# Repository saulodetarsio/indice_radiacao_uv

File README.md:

# Protótipo de um medidor de índice de radiação UV

Primeira parte do projeto

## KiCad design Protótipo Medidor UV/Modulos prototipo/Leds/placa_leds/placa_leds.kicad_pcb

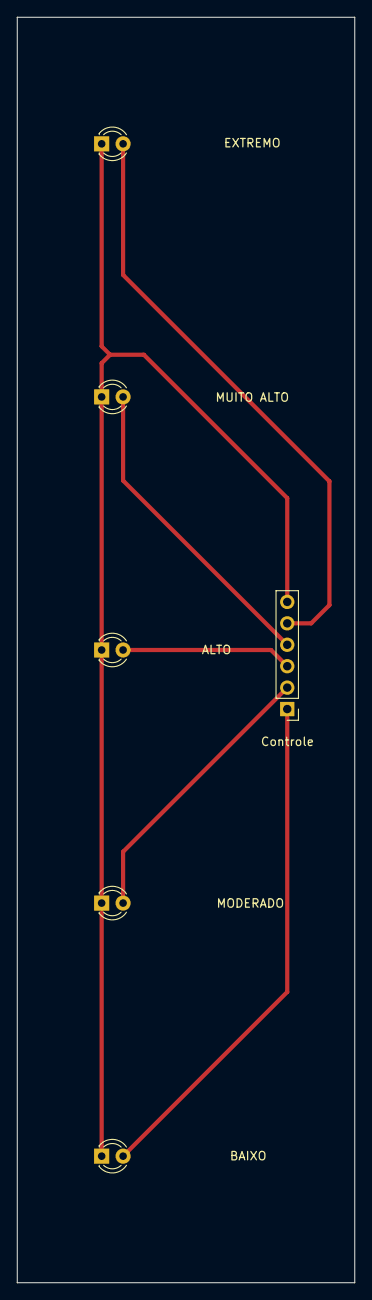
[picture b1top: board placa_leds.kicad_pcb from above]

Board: 2 copper layers, 40.0 x 150.0 mm, 6 parts (0 on the bottom side), 6 nets.

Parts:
ALTO: LED; LED_D3.0mm
BAIXO: LED; LED_D3.0mm
Controle: Conn_01x06_Male; PinHeader_1x06_P2.54mm_Vertical
EXTREMO: LED; LED_D3.0mm
MODERADO: LED; LED_D3.0mm
MUITO ALTO: LED; LED_D3.0mm

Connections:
unnamed: ALTO.1, BAIXO.1, Controle.6, EXTREMO.1, MODERADO.1, MUITO ALTO.1
unnamed: BAIXO.2, Controle.1
unnamed: Controle.2, MODERADO.2
unnamed: ALTO.2, Controle.3
unnamed: Controle.4, MUITO ALTO.2
unnamed: Controle.5, EXTREMO.2

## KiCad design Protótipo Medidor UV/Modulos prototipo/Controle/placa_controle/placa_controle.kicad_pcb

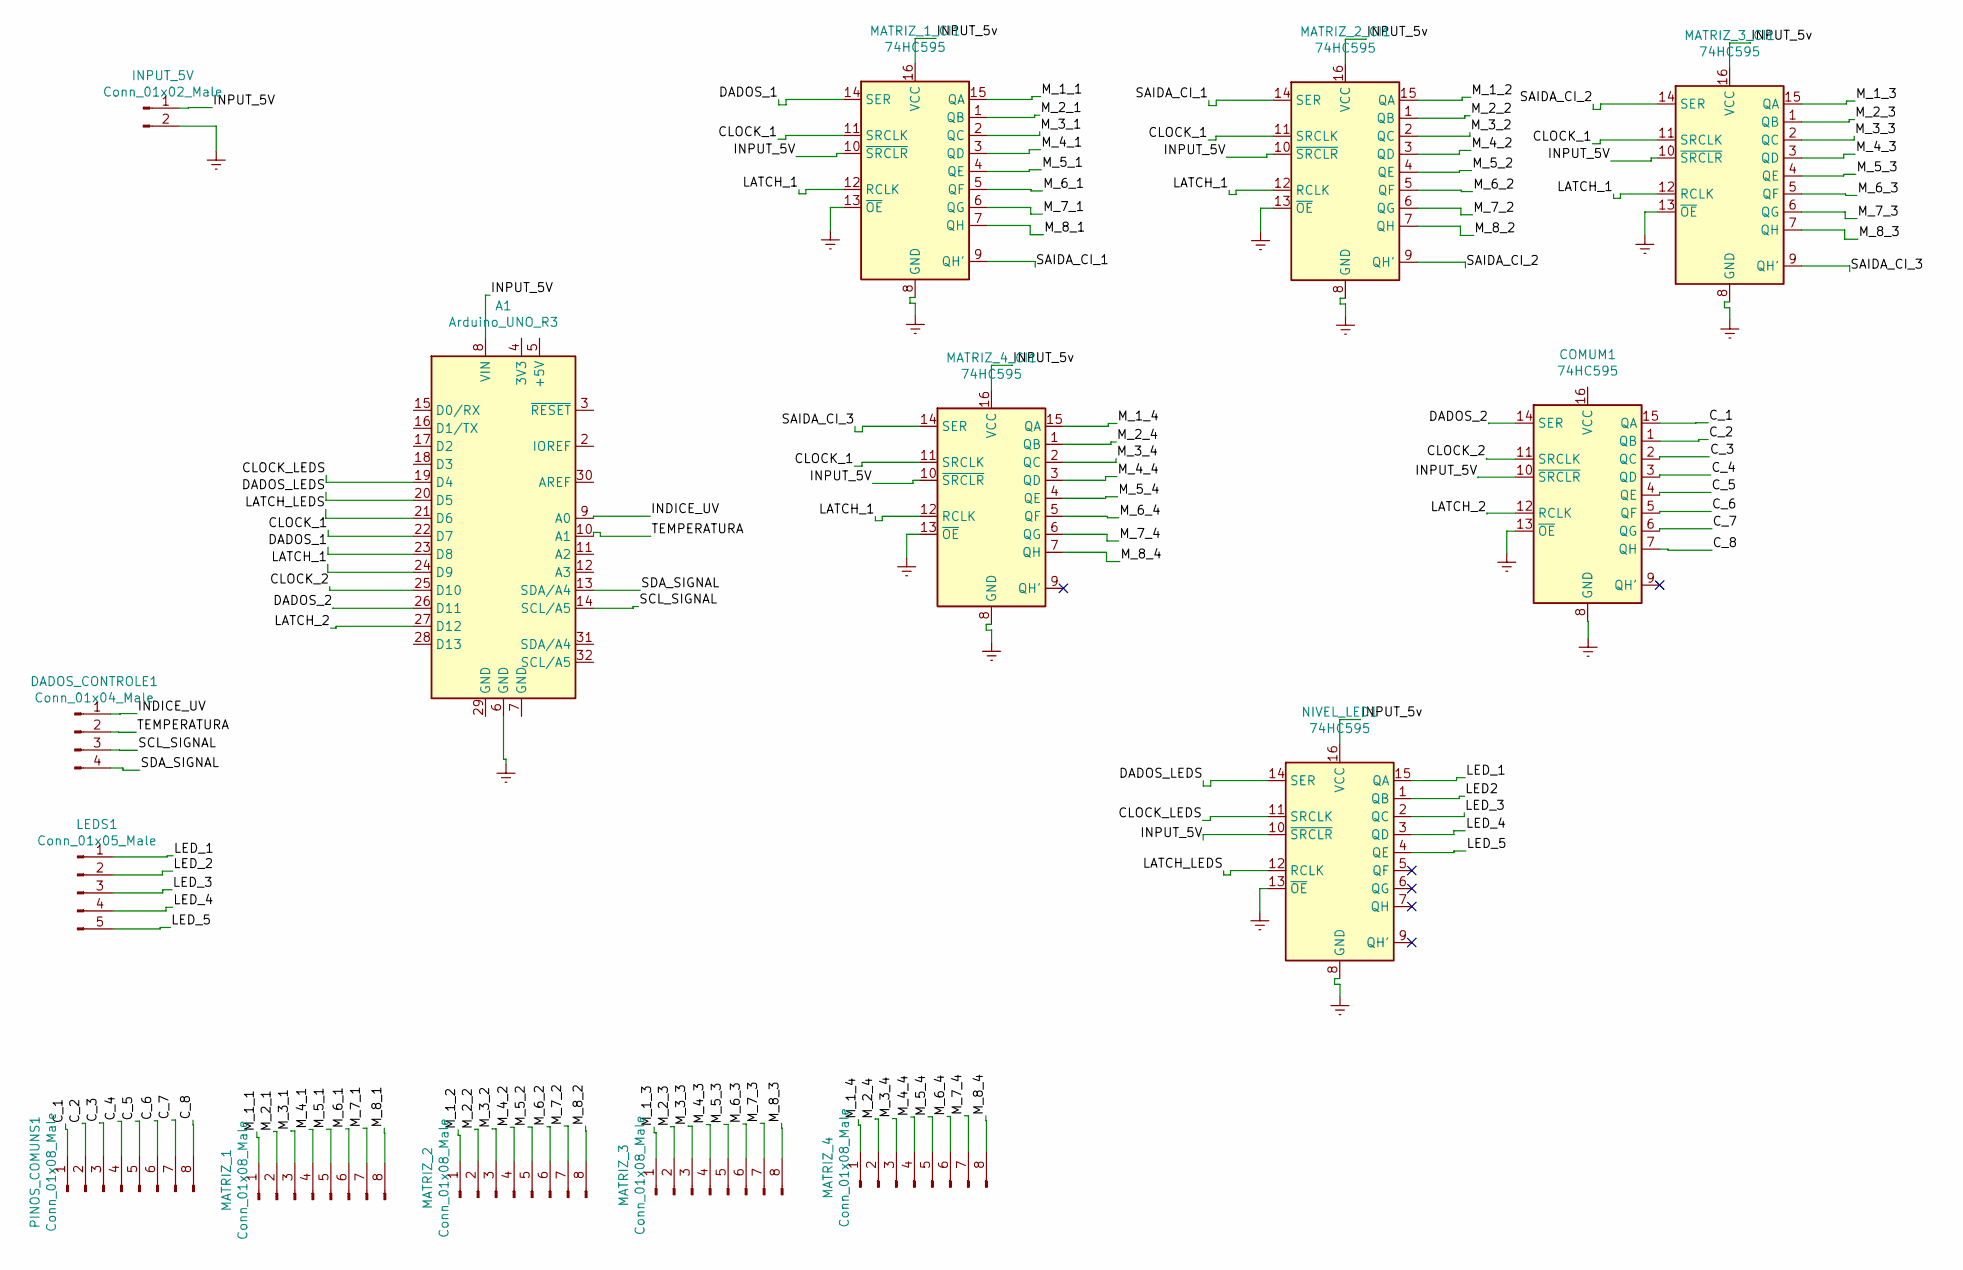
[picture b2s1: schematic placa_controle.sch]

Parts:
A1: Arduino_UNO_R3
COMUM1: 74HC595; DIP-16_W7.62mm
DADOS_CONTROLE1: Conn_01x04_Male; PinHeader_1x04_P2.54mm_Vertical
INPUT_5V: Conn_01x02_Male; PinHeader_1x02_P2.54mm_Vertical
LEDS1: Conn_01x05_Male; PinHeader_1x05_P2.54mm_Vertical
MATRIZ_1, MATRIZ_2, MATRIZ_3, MATRIZ_4: Conn_01x08_Male; PinHeader_1x08_P2.54mm_Vertical
MATRIZ_1_CI1, MATRIZ_2_CI1, MATRIZ_3_CI1, MATRIZ_4_CI1: 74HC595; DIP-16_W7.62mm
NIVEL_LED1: 74HC595; DIP-16_W7.62mm
PINOS_COMUNS1: Conn_01x08_Male; PinHeader_1x08_P2.54mm_Vertical

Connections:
/CLOCK_1: A1.22 (D7), MATRIZ_1_CI1.11 (SRCLK), MATRIZ_2_CI1.11 (SRCLK), MATRIZ_3_CI1.11 (SRCLK), MATRIZ_4_CI1.11 (SRCLK)
/CLOCK_2: A1.25 (D10), COMUM1.11 (SRCLK)
/CLOCK_LEDS: A1.19 (D4), NIVEL_LED1.11 (SRCLK)
/C_1: COMUM1.15 (QA), PINOS_COMUNS1.1
/C_2: COMUM1.1 (QB), PINOS_COMUNS1.2
/C_3: COMUM1.2 (QC), PINOS_COMUNS1.3
/C_4: COMUM1.3 (QD), PINOS_COMUNS1.4
/C_5: COMUM1.4 (QE), PINOS_COMUNS1.5
/C_6: COMUM1.5 (QF), PINOS_COMUNS1.6
/C_7: COMUM1.6 (QG), PINOS_COMUNS1.7
/C_8: COMUM1.7 (QH), PINOS_COMUNS1.8
/DADOS_1: A1.23 (D8), MATRIZ_1_CI1.14 (SER)
/DADOS_2: A1.26 (D11), COMUM1.14 (SER)
/DADOS_LEDS: A1.20 (D5), NIVEL_LED1.14 (SER)
/INDICE_UV: A1.9 (A0), DADOS_CONTROLE1.1
/INPUT_5V: A1.8 (VIN), COMUM1.10 (~SRCLR), INPUT_5V.1, MATRIZ_1_CI1.10 (~SRCLR), MATRIZ_2_CI1.10 (~SRCLR), MATRIZ_3_CI1.10 (~SRCLR), MATRIZ_4_CI1.10 (~SRCLR), NIVEL_LED1.10 (~SRCLR); also elsewhere on the board
/INPUT_5v: MATRIZ_1_CI1.16 (VCC), MATRIZ_2_CI1.16 (VCC), MATRIZ_3_CI1.16 (VCC), MATRIZ_4_CI1.16 (VCC), NIVEL_LED1.16 (VCC)
/LATCH_1: A1.24 (D9), MATRIZ_1_CI1.12 (RCLK), MATRIZ_2_CI1.12 (RCLK), MATRIZ_3_CI1.12 (RCLK), MATRIZ_4_CI1.12 (RCLK)
/LATCH_2: A1.27 (D12), COMUM1.12 (RCLK)
/LATCH_LEDS: A1.21 (D6), NIVEL_LED1.12 (RCLK)
/LED2: NIVEL_LED1.1 (QB)
/LED_1: LEDS1.1, NIVEL_LED1.15 (QA)
/LED_2: LEDS1.2
/LED_3: LEDS1.3, NIVEL_LED1.2 (QC)
/LED_4: LEDS1.4, NIVEL_LED1.3 (QD)
/LED_5: LEDS1.5, NIVEL_LED1.4 (QE)
/M_1_1: MATRIZ_1.1, MATRIZ_1_CI1.15 (QA)
/M_1_2: MATRIZ_2.1, MATRIZ_2_CI1.15 (QA)
/M_1_3: MATRIZ_3.1, MATRIZ_3_CI1.15 (QA)
/M_1_4: MATRIZ_4.1, MATRIZ_4_CI1.15 (QA)
/M_2_1: MATRIZ_1.2, MATRIZ_1_CI1.1 (QB)
/M_2_2: MATRIZ_2.2, MATRIZ_2_CI1.1 (QB)
/M_2_3: MATRIZ_3.2, MATRIZ_3_CI1.1 (QB)
/M_2_4: MATRIZ_4.2, MATRIZ_4_CI1.1 (QB)
/M_3_1: MATRIZ_1.3, MATRIZ_1_CI1.2 (QC)
/M_3_2: MATRIZ_2.3, MATRIZ_2_CI1.2 (QC)
/M_3_3: MATRIZ_3.3, MATRIZ_3_CI1.2 (QC)
/M_3_4: MATRIZ_4.3, MATRIZ_4_CI1.2 (QC)
/M_4_1: MATRIZ_1.4, MATRIZ_1_CI1.3 (QD)
/M_4_2: MATRIZ_2.4, MATRIZ_2_CI1.3 (QD)
/M_4_3: MATRIZ_3.4, MATRIZ_3_CI1.3 (QD)
/M_4_4: MATRIZ_4.4, MATRIZ_4_CI1.3 (QD)
/M_5_1: MATRIZ_1.5, MATRIZ_1_CI1.4 (QE)
/M_5_2: MATRIZ_2.5, MATRIZ_2_CI1.4 (QE)
/M_5_3: MATRIZ_3.5, MATRIZ_3_CI1.4 (QE)
/M_5_4: MATRIZ_4.5, MATRIZ_4_CI1.4 (QE)
/M_6_1: MATRIZ_1.6, MATRIZ_1_CI1.5 (QF)
/M_6_2: MATRIZ_2.6, MATRIZ_2_CI1.5 (QF)
/M_6_3: MATRIZ_3.6, MATRIZ_3_CI1.5 (QF)
/M_6_4: MATRIZ_4.6, MATRIZ_4_CI1.5 (QF)
/M_7_1: MATRIZ_1.7, MATRIZ_1_CI1.6 (QG)
/M_7_2: MATRIZ_2.7, MATRIZ_2_CI1.6 (QG)
/M_7_3: MATRIZ_3.7, MATRIZ_3_CI1.6 (QG)
/M_7_4: MATRIZ_4.7, MATRIZ_4_CI1.6 (QG)
/M_8_1: MATRIZ_1.8, MATRIZ_1_CI1.7 (QH)
/M_8_2: MATRIZ_2.8, MATRIZ_2_CI1.7 (QH)
/M_8_3: MATRIZ_3.8, MATRIZ_3_CI1.7 (QH)
/M_8_4: MATRIZ_4.8, MATRIZ_4_CI1.7 (QH)
/SAIDA_CI_1: MATRIZ_1_CI1.9 (QH'), MATRIZ_2_CI1.14 (SER)
/SAIDA_CI_2: MATRIZ_2_CI1.9 (QH'), MATRIZ_3_CI1.14 (SER)
/SAIDA_CI_3: MATRIZ_3_CI1.9 (QH'), MATRIZ_4_CI1.14 (SER)
/SCL_SIGNAL: A1.14 (SCL/A5), DADOS_CONTROLE1.3
/SDA_SIGNAL: A1.13 (SDA/A4), DADOS_CONTROLE1.4
/TEMPERATURA: A1.10 (A1), DADOS_CONTROLE1.2
Earth: A1.6 (GND), COMUM1.8 (GND), COMUM1.13 (~OE), INPUT_5V.2, MATRIZ_1_CI1.8 (GND), MATRIZ_1_CI1.13 (~OE), MATRIZ_2_CI1.8 (GND), MATRIZ_2_CI1.13 (~OE), MATRIZ_3_CI1.8 (GND), MATRIZ_3_CI1.13 (~OE), MATRIZ_4_CI1.8 (GND), MATRIZ_4_CI1.13 (~OE), NIVEL_LED1.8 (GND), NIVEL_LED1.13 (~OE); also elsewhere on the board

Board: 2 copper layers, 15 parts (0 on the bottom side), 63 nets, no tracks yet.

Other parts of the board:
INPUT_5V1: Conn_01x02_Male; PinHeader_1x02_P2.54mm_Vertical

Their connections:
/INPUT_5V: INPUT_5V1.1; also elsewhere on the board
Earth: INPUT_5V1.2; also elsewhere on the board

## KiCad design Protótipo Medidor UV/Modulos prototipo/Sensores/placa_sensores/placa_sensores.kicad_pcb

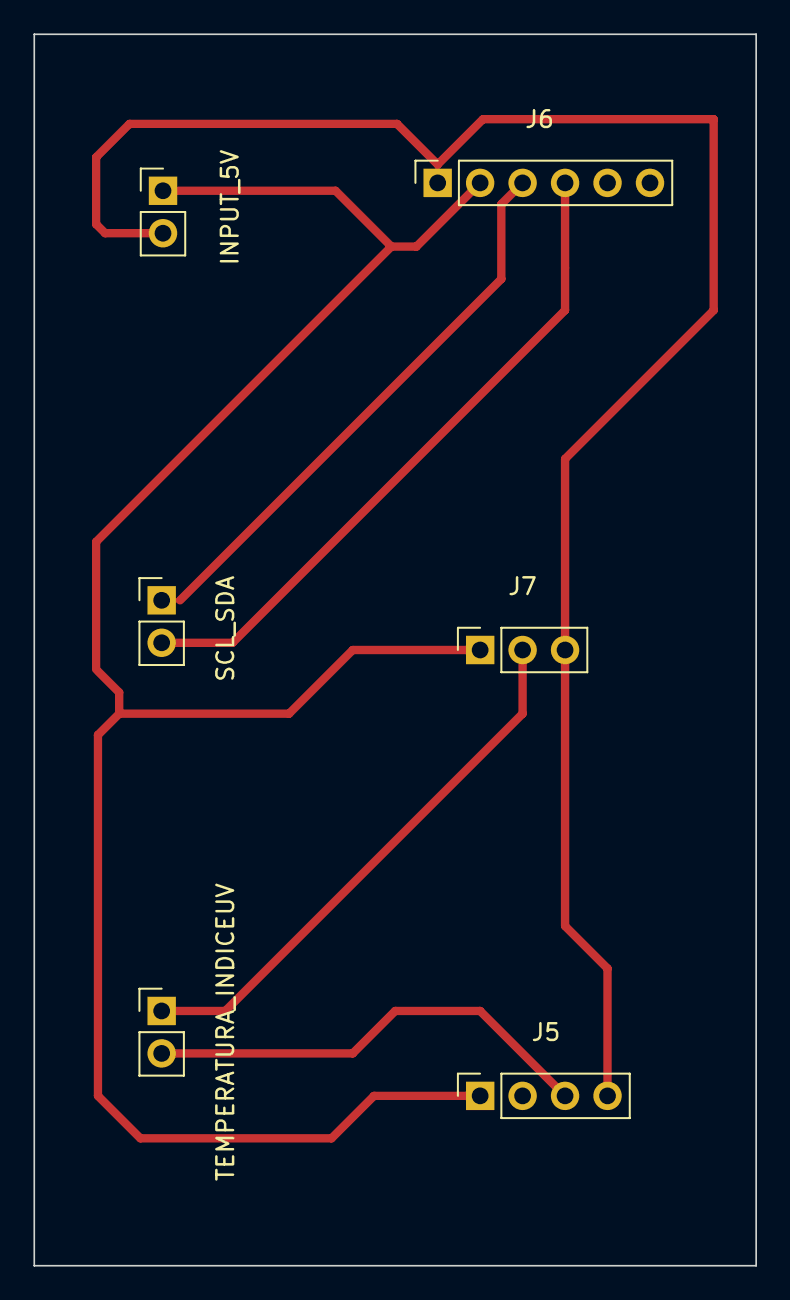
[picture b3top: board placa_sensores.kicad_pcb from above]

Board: 2 copper layers, 43.2 x 73.7 mm, 6 parts (0 on the bottom side), 6 nets.

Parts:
INPUT_5V: Conn_01x02_Male; PinHeader_1x02_P2.54mm_Vertical
J5: Conn_01x04_Female; PinSocket_1x04_P2.54mm_Vertical
J6: Conn_01x06_Female; PinSocket_1x06_P2.54mm_Vertical
J7: Conn_01x03_Female; PinSocket_1x03_P2.54mm_Vertical
SCL_SDA: Conn_01x02_Male; PinHeader_1x02_P2.54mm_Vertical
TEMPERATURA_INDICEUV: Conn_01x02_Male; PinHeader_1x02_P2.54mm_Vertical

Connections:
/ALIMENTACAO_5V: INPUT_5V.1, J5.1, J6.2, J7.1
/SINAL_INDICE_UV: J7.2, TEMPERATURA_INDICEUV.1
/SINAL_SCL: J6.4, SCL_SDA.2
/SINAL_SDA: J6.3, SCL_SDA.1
/SINAL_TEMPERATURA: J5.3, TEMPERATURA_INDICEUV.2
Earth: INPUT_5V.2, J5.4, J6.1, J7.3

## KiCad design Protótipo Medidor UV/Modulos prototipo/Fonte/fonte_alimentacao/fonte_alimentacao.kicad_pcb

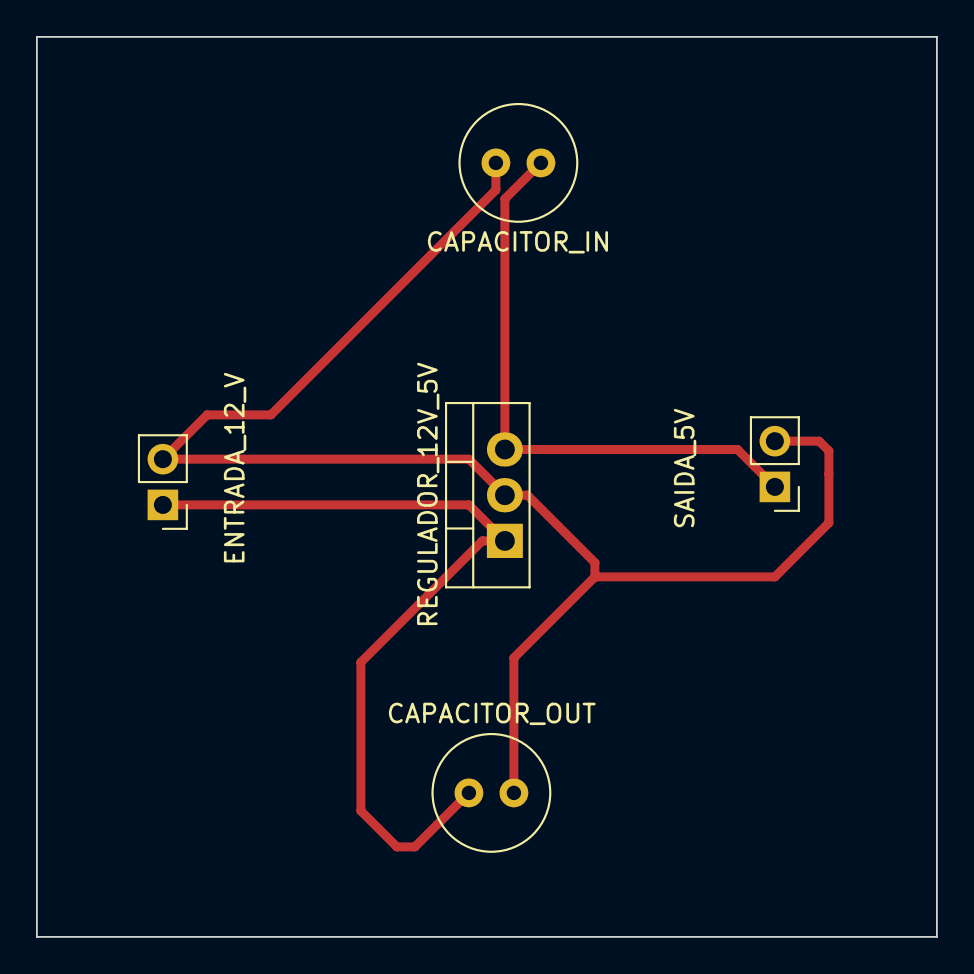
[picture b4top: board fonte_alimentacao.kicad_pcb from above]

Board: 2 copper layers, 50.0 x 50.0 mm, 5 parts (0 on the bottom side), 3 nets.

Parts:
CAPACITOR_IN: C; C_Radial_D6.3mm_H5.0mm_P2.50mm
CAPACITOR_OUT: C; C_Radial_D6.3mm_H5.0mm_P2.50mm
ENTRADA_12_V: Conn_01x02_Male; PinHeader_1x02_P2.54mm_Vertical
REGULADOR_12V_5V: LM7805_TO220; TO-220-3_Vertical
SAIDA_5V: Conn_01x02_Male; PinHeader_1x02_P2.54mm_Vertical

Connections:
unnamed: CAPACITOR_OUT.1, ENTRADA_12_V.1, REGULADOR_12V_5V.1
unnamed: CAPACITOR_IN.2, CAPACITOR_OUT.2, ENTRADA_12_V.2, REGULADOR_12V_5V.2, SAIDA_5V.2
unnamed: CAPACITOR_IN.1, REGULADOR_12V_5V.3, SAIDA_5V.1

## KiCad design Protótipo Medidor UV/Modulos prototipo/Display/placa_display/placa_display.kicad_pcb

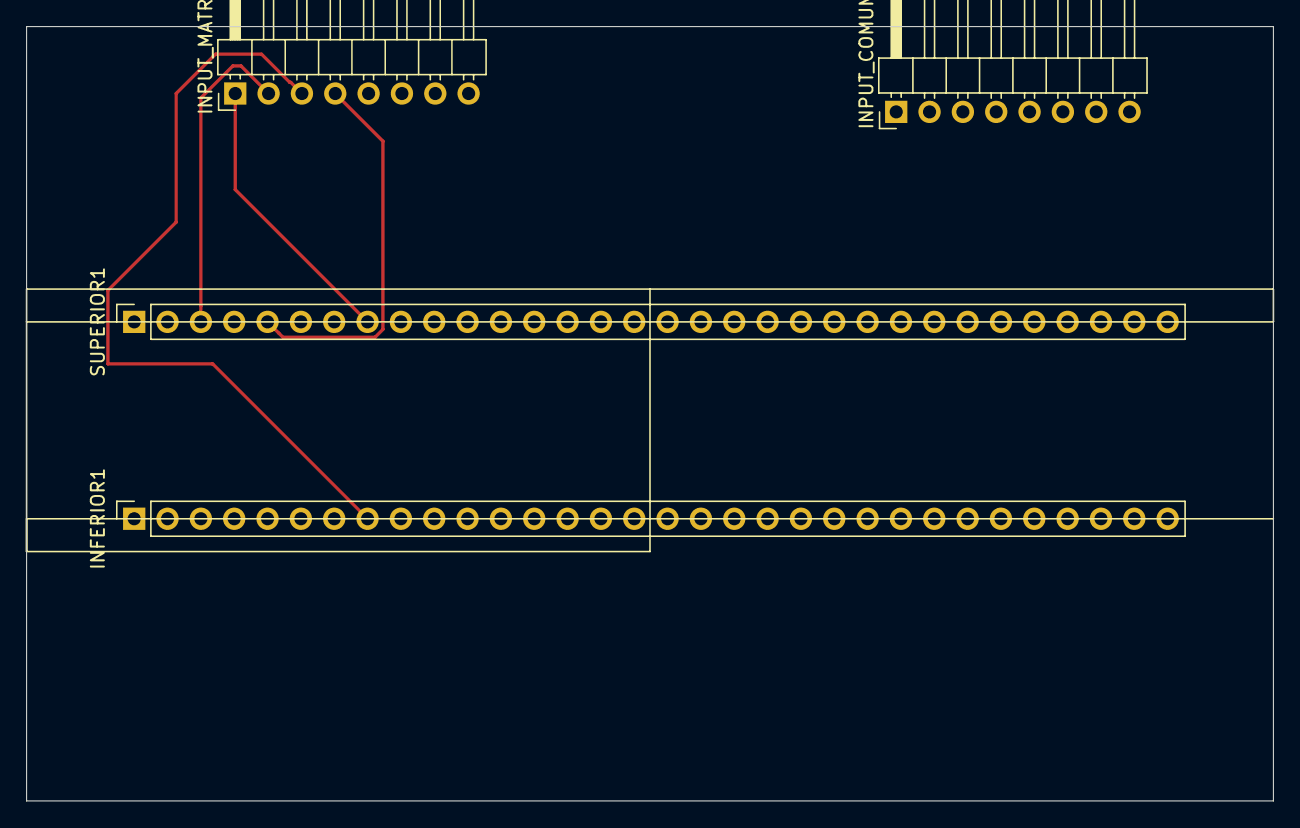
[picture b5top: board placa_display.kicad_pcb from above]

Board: 2 copper layers, 95.0 x 59.0 mm, 4 parts (0 on the bottom side), 16 nets.

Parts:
INFERIOR1: Conn_01x32_Female; PinSocket_1x32_P2.54mm_Vertical
INPUT_COMUM1: Conn_01x08_Male; PinHeader_1x08_P2.54mm_Horizontal
INPUT_MATRIZ_1: Conn_01x08_Male; PinHeader_1x08_P2.54mm_Horizontal
SUPERIOR1: Conn_01x32_Female; PinSocket_1x32_P2.54mm_Vertical

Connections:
/C1: INPUT_COMUM1.1, SUPERIOR1.4, SUPERIOR1.12, SUPERIOR1.20, SUPERIOR1.28
/C2: INFERIOR1.3, INFERIOR1.11, INFERIOR1.19, INFERIOR1.27, INPUT_COMUM1.2
/C3: INFERIOR1.4, INFERIOR1.12, INFERIOR1.20, INFERIOR1.28, INPUT_COMUM1.3
/C4: INPUT_COMUM1.4, SUPERIOR1.7, SUPERIOR1.15, SUPERIOR1.23, SUPERIOR1.31
/C5: INFERIOR1.6, INFERIOR1.14, INFERIOR1.22, INFERIOR1.30, INPUT_COMUM1.5
/C6: INPUT_COMUM1.6, SUPERIOR1.6, SUPERIOR1.14, SUPERIOR1.22, SUPERIOR1.30
/C7: INPUT_COMUM1.7, SUPERIOR1.1, SUPERIOR1.9, SUPERIOR1.17, SUPERIOR1.25
/C8: INPUT_COMUM1.8, SUPERIOR1.2, SUPERIOR1.10, SUPERIOR1.18, SUPERIOR1.26
/M_1_1: INPUT_MATRIZ_1.1, SUPERIOR1.8
/M_1_2: INPUT_MATRIZ_1.2, SUPERIOR1.3
/M_1_3: INFERIOR1.8, INPUT_MATRIZ_1.3
/M_1_4: INPUT_MATRIZ_1.4, SUPERIOR1.5
/M_1_5: INFERIOR1.1, INPUT_MATRIZ_1.5
/M_1_6: INFERIOR1.7, INPUT_MATRIZ_1.6
/M_1_7: INFERIOR1.2, INPUT_MATRIZ_1.7
/M_1_8: INFERIOR1.5, INPUT_MATRIZ_1.8

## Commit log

2020-07-29 primeiro commit
2020-07-29 Subindo todos os materiais e artefatos gerados durante a execução do projeto
